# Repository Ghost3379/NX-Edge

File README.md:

# NX-Edge

> **Modular Embedded Development Platform**  
> *M.2 2260 Key B • 6-Layer Stackup • ESP32-S3 Dual-Core 240MHz • Autonomous LiPo Power-Path & Fuel Gauge • Dual-Antenna RF Front-End • 9-DOF IMU • I2S Audio Amp • 4-bit MicroSD*

---

<p align="center">
  <em>NX-Edge Top View — 100% single-sided top assembly with 45° ESP32-S3, QSPI Flash, BNO085 IMU, RV-3028 RTC, MAX98357A Audio Amp, MicroSD slot, LiPo Charger & Fuel Gauge.</em>
</p>

<p align="center">
  <em>NX-Edge Bottom View — Flat single-sided surface with M.2 Key B docking fingers, NO NVME warning, IMU coordinate triad, cut-safe jumpers [SW] & [LED], and GAIN test pad.</em>
</p>

---

> [!TIP]
> 📖 **Technical Documentation Available:**  
> * **[NX-Edge Hardware Reference Manual](docs/HARDWARE_MANUAL.md):** Detailed pinouts, subsystem floorplan, I2C register maps, power-path precautions, and quickstart code.
> * **[NX-Edge RF Design Guide](docs/RF_DESIGN_GUIDE.md):** 2.4 GHz transmission line impedance derivations ($Z_0 = 51.44\,\Omega$), stackup equations, and matching network BOM values.

---

## Overview

The **NX-Edge** is an embedded development board based on the ESP32-S3, built in an M.2 2260 form factor. It integrates power management, audio amplification, 9-DOF motion tracking, RTC, and microSD storage onto a single board, designed to interface with custom carrier boards via an M.2 Key B connector or edge breakout headers.

Built on a **6-layer PCB** with **100% single-sided component placement** (zero components on the bottom layer):

* **M.2 2260 Form Factor ($22 \times 60\text{ mm}$):** Fits the ESP32-S3 and all peripherals within the 60 mm board length.
* **M.2 Key B Edge Connector (75 pins):** Custom pinout routing power, audio, I2C, UART, SDMMC, and all free GPIOs to carrier boards.
* **Edge Breakouts (2.54 mm pitch):** 15 edge breakout holes for bench testing and wiring. The left side breaks out logic/power/I2C/UART, and the right side breaks out NeoPixel and speaker outputs.
* **Flat Bottom Surface:** 100% single-sided top assembly with zero components on the bottom, leaving the back flat for low-profile mounting.

> [!IMPORTANT]
> **NX Custom Maker Interconnect (Non-PC Hardware):**  
> While the board utilizes the standard mechanical **M.2 Key B form factor and connector**, the pinout is a **custom, high-power maker standard** (similar to SparkFun MicroMod). The M.2 connector routes raw battery power, high-current 5V rails, speaker outputs, and 3.3V GPIOs directly to custom carrier boards. **Do NOT plug this board into a standard PC motherboard M.2 NVMe/SATA slot.**

---

## Current Hardware Implementation Status

| Subsystem / Block | Status | Key Components & Implementation Details |
| :--- | :---: | :--- |
| **Compute Core** | **Routed** | ESP32-S3 (bare QFN-56 @ 45°), 40 MHz 2016 crystal with symmetrical wings, decoupling network on power rails. |
| **Flash Memory** | **Routed** | 16 MB Winbond `W25Q128JVPIQ` (WSON-8), inline decoupling, Quad-SPI bus routed on internal Layer 3 stripline. |
| **RF Front-End** | **Routed** | Ignion `NN02-201` ceramic antenna + Hirose U.FL receptacle + Infineon `BGS12WN6` SPDT RF switch (`RF_CTRL`). |
| **USB Type-C** | **Routed** | Reversible Type-C receptacle, `USBLC6-2SC6` ESD array, dual $5.1\,\text{k}\Omega$ CC pulldowns (`R20`/`R21`), D+/D- internal stripline. |
| **LiPo Charging** | **Routed** | TI `BQ25170` autonomous linear charger (600–800 mA), status LED, horizontal JST-PH 2.0mm connector (`P1`/`P2`). |
| **Battery Power Switch** | **Routed** | Solder jumper & switch pads `JP2` (`[ SW ]`) to wire a physical power toggle switch (must be ON to charge). |
| **Buck Regulator** | **Routed** | TI `TLV62569` synchronous buck converter delivering continuous **3.3V @ 2.0A** with low ripple. |
| **Fuel Gauge** | **Routed** | Maxim `MAX17048` ModelGauge™ I2C fuel gauge (`0x36`) for cell voltage ($V_{CELL}$) and SoC% without IR drop. |
| **NeoPixel Driver** | **Routed** | P-FET `Q2` (DMP3130L-7) + NPN `Q3` (BC847W) on `IO12` with 3 castellated pads (`VN`, `NPD_IN`, `GND`) for high-power strips. |
| **Onboard Indicators**| **Routed** | Onboard RGB NeoPixel (WS2812B/SK6812) powered from `VN` + User LED (LED13 / `D3`) with resistor `R13`. |
| **6-Layer Stackup** | **Routed** | 6-layer stackup with 0.45 mm / 0.25 mm standard through-hole vias for clean signal integrity. |
| **MicroSD Slot** | **Routed** | Molex 105162 push-pull slot running in native **4-bit hardware SDMMC** mode via dedicated internal stripline bus. |
| **Motion Sensor** | **Routed** | CEVA / Hillcrest Labs `BNO085` 9-DOF IMU with dedicated 32.768 kHz quartz crystal and sensor-fusion engine. |
| **Audio Amplifier** | **Routed** | Maxim `MAX98357A` I2S Class-D mono amplifier delivering up to 3.2W into 4Ω directly from `VIN` (Bridge-Tied Load speaker output). |
| **RTC Subsystem** | **Routed** | Micro Crystal `RV-3028-C7` extreme low-power ($45\,\text{nA}$) real-time clock with backup capacitor. |
| **Hardware Buttons** | **Routed** | Dual Alps `SKTAAAE010` ($0.53\text{ mm}$ height) tactile buttons for **BOOT** (`IO0`) and **RST** with hardware Power-On-Reset (POR) delay circuit. |
| **Routing Status** | **100% Complete** | 100% routed on all 6 layers using **standard through-hole vias only** (0 blind, 0 buried). |

---

## 6-Layer Stackup Architecture

To ensure signal integrity and separate the 2.4 GHz RF stage from digital signal buses, the NX-Edge uses a **6-layer symmetrical stackup**:

| Layer | KiCad Layer | Type | Copper Role & Signal Integrity Function |
| :---: | :---: | :---: | :--- |
| **L1** | `F.Cu` | Mixed / Top | Component mounting, 2.4 GHz RF transmission line, localized power pours (`VIN`, `+3V3`, `VBAT`). |
| **L2** | `In1.Cu` | Plane | **Solid Ground Plane (GND):** Return path and shield directly below Top layer. |
| **L3** | `In2.Cu` | Stripline Sig | **Internal Signals:** Shielded striplines for **USB D+/D-**, **Flash Quad-SPI**, and **SDMMC**. |
| **L4** | `In3.Cu` | Power Plane | **Power Plane Mosaic:** Low-impedance internal distribution for `+3V3`, `VBUS`, and `VBAT`. |
| **L5** | `In4.Cu` | Plane | **Secondary Solid Ground Plane (GND):** Complete ground shield referencing Bottom layer. |
| **L6** | `B.Cu` | Mixed / Bottom | Non-critical escape routing, switched `VN` power plane, M.2 docking fingers, and edge test pads. |

* **Via Geometry & Cost Efficiency:** Optimized to **0.45 mm pad diameter / 0.25 mm drill hole** (0.1 mm annular ring). The entire board is routed using **standard through-hole vias only** (0 blind, 0 buried, and 0 laser micro-vias), keeping prototype fabrication compatible with standard, low-cost fab pools.

---

## Power Architecture & Power-Path Topology

The NX-Edge implements an autonomous, low-loss **Power-Path management architecture**:

```text
  USB-C (VBUS 5V) ──► [Schottky D2] ──────────┐
                                              │
  LiPo (VBAT) ────► [Hard-Cut JP2] ──► [Q1] ──┴─► [ VIN ] (Automatic System Rail)
                                        ▲           │
                                        │ Gate      ├─► [TLV62569 Buck] ──► +3V3 (2.0A)
                                  (VBUS Controlled) │
                                                    ├─► [MAX17048 Gauge] (I2C SoC Monitoring)
                                                    │
                                                    └─► [Q2 P-FET / Q3 NPN] ──► VN (Switched NeoPixel Rail)
                                                              ▲
                                                              │ GPIO12 (CTRL_NP)
```

1. **Automatic Power-Path Node (`VIN`):**
   * Sourced through Schottky diode from USB `VBUS` ($5.0\text{V}$) or low-loss P-MOSFET from battery `VBAT` ($3.7\text{–}4.2\text{V}$).
   * **USB Connected:** `VBUS` holds the P-FET gate high, completely isolating the battery from system discharge. `VIN` runs directly on USB power ($\approx 4.8\text{–}5.0\text{V}$).
   * **Battery Only:** When USB is disconnected, a gate pull-down immediately engages the P-FET ($R_{DS(on)} \approx 30\text{ m}\Omega$), supplying `VIN` with virtually zero voltage drop.
2. **System Buck Regulator (`TLV62569`):**
   * Synchronous step-down buck converter delivering **$3.3\text{V} @ \mathbf{2.0\text{A}}$ continuous** with $>95\%$ efficiency.
   * Powers the ESP32-S3, Flash, sensors, and peripherals cleanly without thermal throttling.
3. **Autonomous LiPo Charger (`BQ25170`):**
   * Standalone linear charger powered from `VBUS` configured for $600\text{–}800\text{ mA}$ charging with NTC thermistor input.
   * **Decoupled Charging:** Because the system and external LEDs run from `VIN`, charging current is never hijacked by system load.
4. **ModelGauge™ Fuel Gauge (`MAX17048`):**
   * Precision I2C fuel gauge (`0x36`) monitoring cell voltage directly at the battery connector. Reports cell voltage ($V_{CELL}$ in mV), State of Charge (SOC %), and rate of change over I2C without needing external ADC dividers.
5. **Smart NeoPixel Power-Cut (`VN`):**
   * High-side P-MOSFET `Q2` driven by NPN BJT `Q3` controlled via **GPIO12 (`CTRL_NP`)**.
   * In Standby/Deep Sleep (`CTRL_NP = LOW`), power to both onboard and external NeoPixels is cut to $0.0\text{V}$, eliminating quiescent current draw.

---

## RF Front-End & Antenna Switch

* **RF Switch:** Infineon **`BGS12WN6`** SPDT switch ($0.7 \times 1.1\text{ mm}$) rated up to $6\text{ GHz}$ with $<0.3\text{ dB}$ insertion loss.
* **50Ω Transmission Lines:** All RF lines routed on `F.Cu` with $W = 0.150\,\text{mm}$ over $0.100\,\text{mm}$ prepreg ($Z_0 = 51.44\,\Omega$, $\text{VSWR} = 1.028:1$). See the **[RF Design Guide](docs/RF_DESIGN_GUIDE.md)** for detailed math and matching BOM values.
* **Control:** Controlled via **`RF_CTRL`** (`GPIO10`):
  * **Low (Default):** On-board high-efficiency **Ignion NN02-201** ceramic chip antenna with 50Ω lumped matching network (`C13`, `L3`, `L2`).
  * **High:** Micro-coaxial **Hirose U.FL / IPEX** receptacle for external antenna routing out of metal, carbon fiber, or shielded enclosures.

---

## Mechanical Specifications

* **Form Factor:** M.2 2260 Key B ($22.0\text{ mm} \times 60.0\text{ mm}$).
* **Connector Type:** 75-pin M.2 Key B card edge connector.
* **PCB Thickness:** **$0.80\,\text{mm} \pm 10\%$** ($0.8\text{ mm}$ finished thickness, compliant with the official PCI-SIG M.2 Card Electromechanical Specification).
* **Component Clearance:** 100% single-sided top placement. Completely flat bottom surface (Zero-Z) for ultra-low-profile carrier mounting.
* **Silkscreen & Hardware Annotations:**
  * **`NO NVME`** boxed warning over bottom gold fingers to prevent accidental insertion into standard PC motherboard slots.
  * Dual-purpose **`B ▽`** marker designating both `SW2` (BOOT) and the mechanical Key B notch.
  * **`[ SW ]`** (`JP2`) and **`[ LED ]`** (`JP1`) boxed cut-jumpers with internal copper keepouts beneath the cut bridge.
  * **`G`** silkscreen marking audio GAIN test point `TP1`.
  * IMU 3-axis coordinate triad ($X, Y, Z$) and chip boundary outline.
  * MicroSD card insertion icon with contact orientation.
* **Edge Breakouts (2.54 mm pitch):** 15 edge breakout holes:
  * **Left Edge (Logic/Power):** `J9` (6-pin: `3V3`, `GND`, `RST`, `IO0`, `IO1`, `IO11`) and `J5` (4-pin: `IO8`/SDA, `IO9`/SCL, `RX`, `TX`).
  * **Right Edge (Power/Audio):** `J7` (3-pin: NeoPixel `VN`, `NPD_IN`, `GND`) and `J2` (2-pin: Speaker `Audio+`, `Audio-`).
  * *Breadboard & Prototyping Note:* While each individual rail uses standard 2.54 mm pitch and both sides align at the exact same height, the $22.0\text{ mm}$ board width is dictated by the M.2 standard and does not fall on a 2.54 mm grid ($22\text{ mm} \approx 8.66\text{ pitches}$). Vertical pin headers populated on both edges simultaneously will not span a single breadboard across the center ravine.  
    **Recommendation:** Solder pin headers to the IO/logic side (`J9`/`J5`) to plug into a breadboard. For the power/output side (`J7` NeoPixel and `J2` Audio), direct wire soldering or fly-leads are recommended anyway for power delivery and signal integrity—or simply leave them unpopulated if not needed.

---

## License & Credits

* **Hardware Design:** Licensed under the [CERN Open Hardware Licence Version 2 - Strongly Reciprocal (CERN-OHL-S)](https://ohwr.org/cernohl).
* **Engineering & Ownership:** Conceptualized, engineered, schematics, PCB layout, and testing by [@Ghost3379](https://github.com/Ghost3379).
* **Tooling & AI Transparency:** Antigravity IDE (Gemini 3.8) was used for brainstorming and documentation assistance. All hardware architecture, schematics, routing, and layout decisions are 100% human-designed and verified.

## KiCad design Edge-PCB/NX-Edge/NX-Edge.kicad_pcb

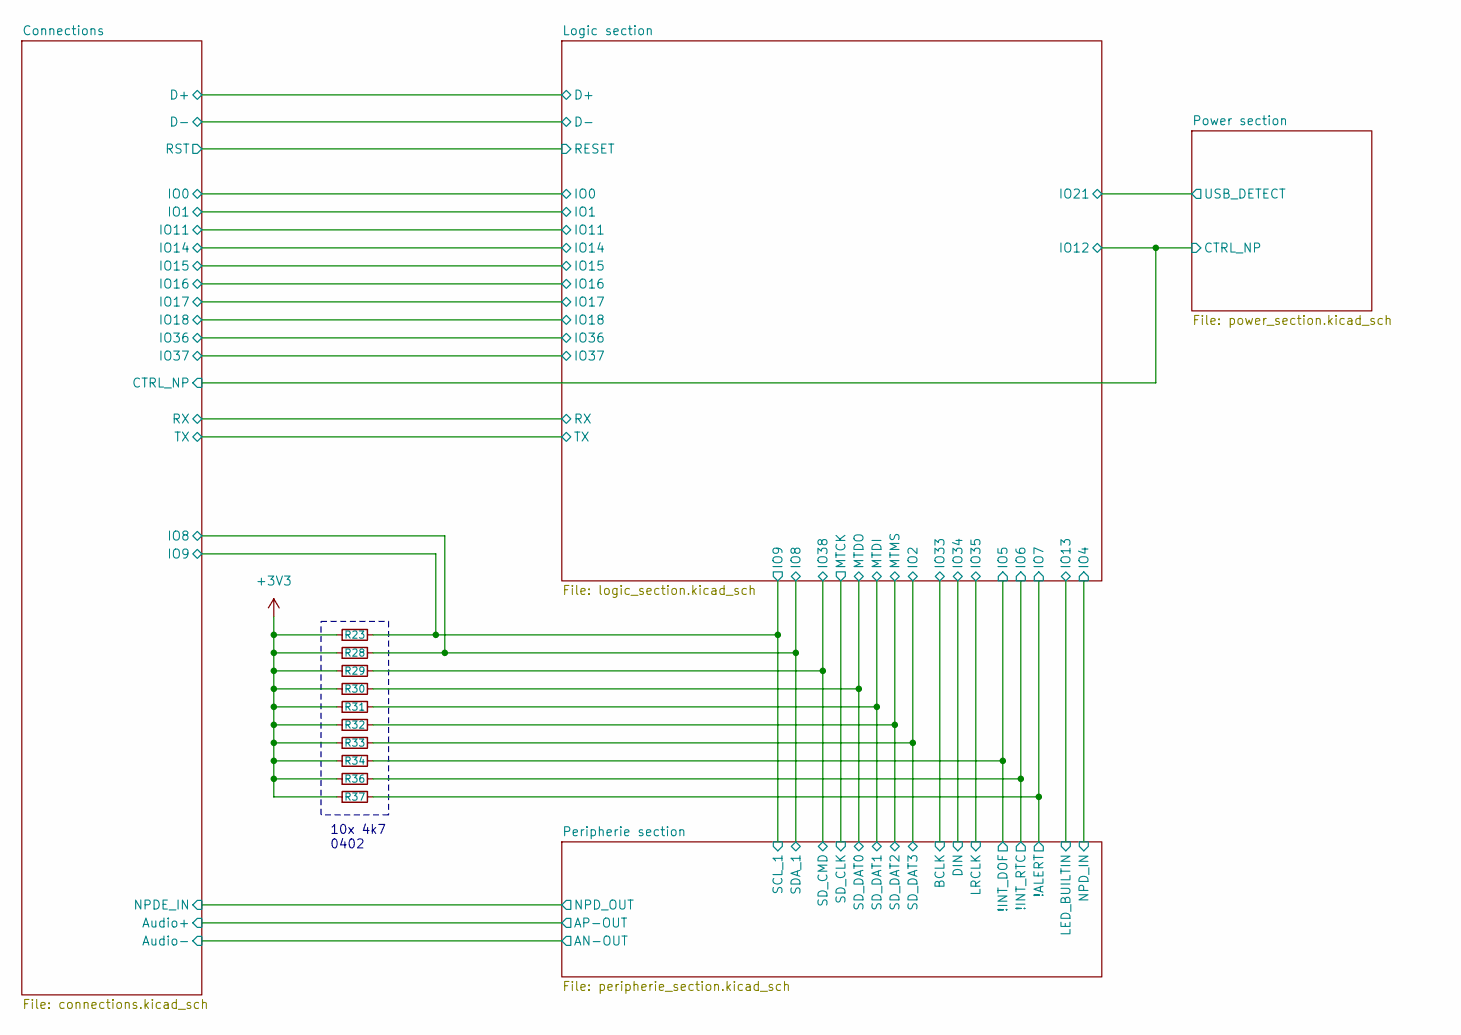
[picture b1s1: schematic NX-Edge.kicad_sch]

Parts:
R23, R28, R29, R30, R31, R32, R33, R34, R36, R37: 4k7; R_0402_1005Metric

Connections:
+3V3: R23.1, R28.1, R29.1, R30.1, R31.1, R32.1, R33.1, R34.1, R36.1, R37.1; also elsewhere on the board
/Connections/IO8: R28.2; also elsewhere on the board
/Connections/IO9: R23.2; also elsewhere on the board
/Logic section/IO2: R33.2; also elsewhere on the board
/Logic section/IO5: R34.2; also elsewhere on the board
/Logic section/IO6: R36.2; also elsewhere on the board
/Logic section/IO7: R37.2; also elsewhere on the board
/Logic section/IO38: R29.2; also elsewhere on the board
/Logic section/MTDI: R31.2; also elsewhere on the board
/Logic section/MTDO: R30.2; also elsewhere on the board
/Logic section/MTMS: R32.2; also elsewhere on the board

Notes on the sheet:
10x 4k7 0402

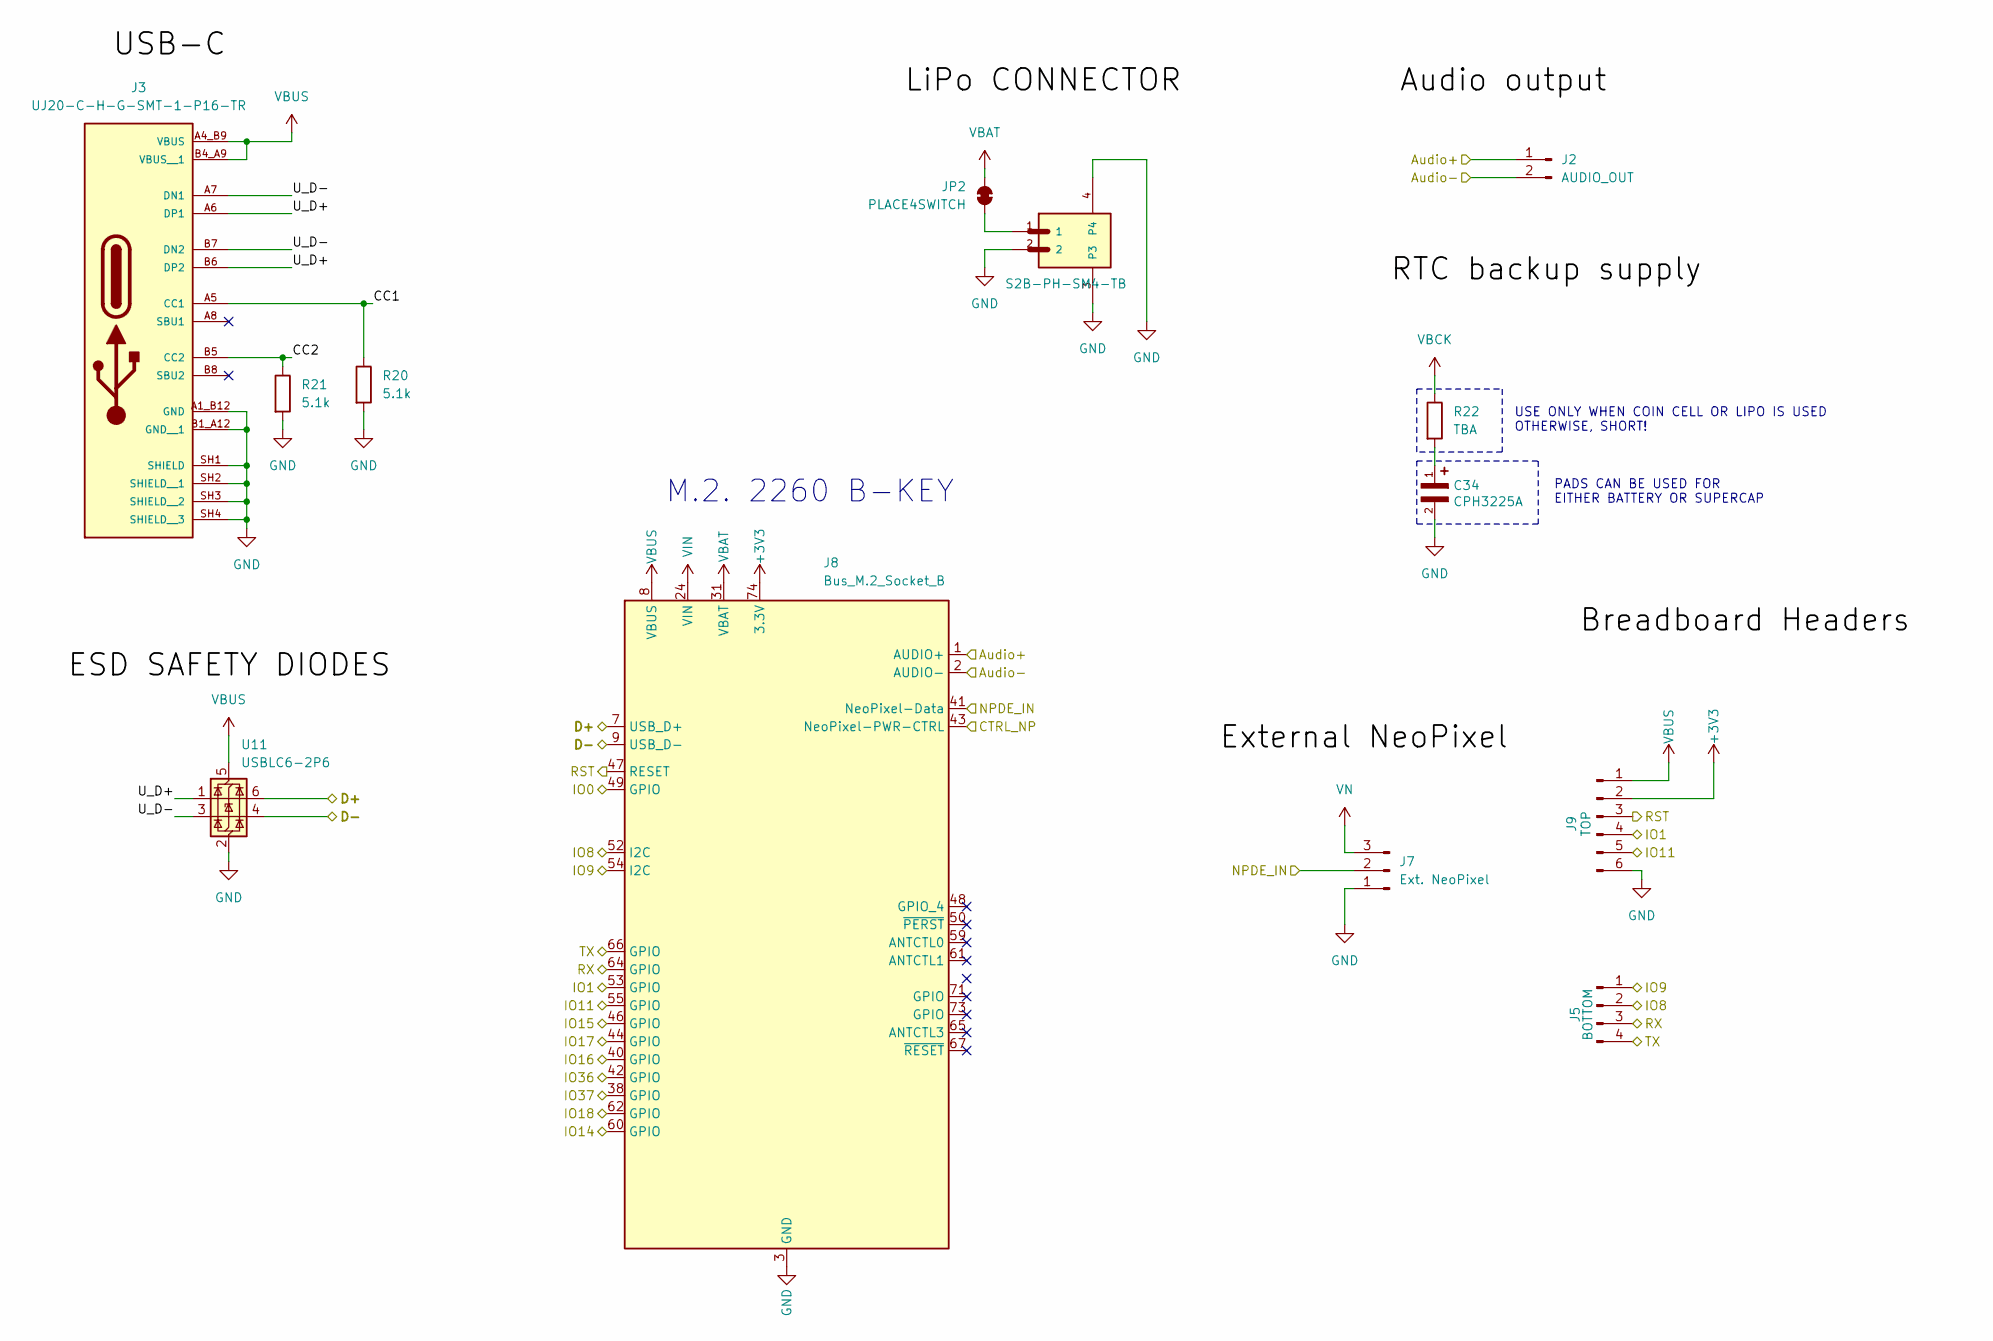
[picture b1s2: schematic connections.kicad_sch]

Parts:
C34: CPH3225A; CAPCP3225X100N
J2: AUDIO_OUT; PinHeader_1x02_P2.54mm_Vertical
J3: UJ20-C-H-G-SMT-1-P16-TR; SAMESKY_UJ20-C-H-G-SMT-1-P16-TR; PARTREV 1.0
J5: BOTTOM; PinHeader_1x04_P2.54mm_Vertical
J7: Ext. NeoPixel; PinHeader_1x03_P2.54mm_Vertical
J8: Bus_M.2_Socket_B; M.2_2260-xx-B
J9: TOP; PinHeader_1x06_P2.54mm_Vertical
JP2: PLACE4SWITCH; SolderJumper-2_P1.3mm_Bridged_Pad1.0x1.5mm
P1: S2B-PH-SM4-TB; JST_S2B-PH-SM4-TB
R20, R21: 5.1k; R_0402_1005Metric
R22: TBA; R_0402_1005Metric
U11: USBLC6-2P6; SOT-666

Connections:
+3V3: J8.68 (3.3V), J8.70 (3.3V), J8.72 (3.3V), J8.74 (3.3V), J9.2; also elsewhere on the board
/Connections/Audio+: J2.1, J8.1 (AUDIO+); also elsewhere on the board
/Connections/Audio-: J2.2, J8.2 (AUDIO-); also elsewhere on the board
/Connections/CC1: J3.A5 (CC1), R20.1
/Connections/CC2: J3.B5 (CC2), R21.1
/Connections/CTRL_NP: J8.43 (NeoPixel-PWR-CTRL); also elsewhere on the board
/Connections/D+: J8.7 (USB_D+), U11.6 (I/O1); also elsewhere on the board
/Connections/D-: J8.9 (USB_D-), U11.4 (I/O2); also elsewhere on the board
/Connections/IO0: J8.49 (GPIO); also elsewhere on the board
/Connections/IO1: J8.53 (GPIO), J9.4; also elsewhere on the board
/Connections/IO8: J5.2, J8.52 (I2C); also elsewhere on the board
/Connections/IO9: J5.1, J8.54 (I2C); also elsewhere on the board
/Connections/IO11: J8.55 (GPIO), J9.5; also elsewhere on the board
/Connections/IO14: J8.60 (GPIO); also elsewhere on the board
/Connections/IO15: J8.46 (GPIO); also elsewhere on the board
/Connections/IO16: J8.40 (GPIO); also elsewhere on the board
/Connections/IO17: J8.44 (GPIO); also elsewhere on the board
/Connections/IO18: J8.62 (GPIO); also elsewhere on the board
/Connections/IO36: J8.42 (GPIO); also elsewhere on the board
/Connections/IO37: J8.38 (GPIO); also elsewhere on the board
/Connections/NPDE_IN: J7.2, J8.41 (NeoPixel-Data); also elsewhere on the board
/Connections/RST: J8.47 (RESET), J9.3; also elsewhere on the board
/Connections/RX: J5.3, J8.64 (GPIO); also elsewhere on the board
/Connections/TX: J5.4, J8.66 (GPIO); also elsewhere on the board
/Connections/U_D+: J3.A6 (DP1), J3.B6 (DP2), U11.1 (I/O1)
/Connections/U_D-: J3.A7 (DN1), J3.B7 (DN2), U11.3 (I/O2)
GND: C34.2, J3.A1_B12 (GND), J3.B1_A12 (GND__1), J3.SH1 (SHIELD), J3.SH2 (SHIELD__1), J3.SH3 (SHIELD__2), J3.SH4 (SHIELD__3), J7.1, J8.3 (GND), J8.5 (GND), J8.11 (GND), J8.21 (GND), J8.23 (GND), J8.25 (GND), J8.27 (GND), J8.28 (GND), J8.29 (GND), J8.30 (GND), J8.32 (GND), J8.34 (GND), J8.36 (GND), J8.39 (GND), J8.45 (GND), J8.51 (GND), J8.57 (GND), J8.63 (GND), J8.69 (GND), J8.75 (GND), J9.6, P1.2, P1.3, P1.4, R20.2, R21.2, U11.2 (GND); also elsewhere on the board
unnamed: C34.1, R22.2
unnamed: JP2.2 (B), P1.1
VBAT: J8.31 (VBAT), J8.33 (VBAT), J8.35 (VBAT), J8.37 (VBAT), JP2.1 (A); also elsewhere on the board
VBCK: R22.1; also elsewhere on the board
VBUS: J3.A4_B9 (VBUS), J3.B4_A9 (VBUS__1), J8.4 (VBUS), J8.6 (VBUS), J8.8 (VBUS), J8.10 (VBUS), J9.1, U11.5 (VBUS); also elsewhere on the board
VIN: J8.20 (VIN), J8.22 (VIN), J8.24 (VIN), J8.26 (VIN); also elsewhere on the board
VN: J7.3; also elsewhere on the board

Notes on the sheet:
USE ONLY WHEN COIN CELL OR LIPO IS USED OTHERWISE, SHORT!
PADS CAN BE USED FOR EITHER BATTERY OR SUPERCAP
M.2. 2260 B-KEY

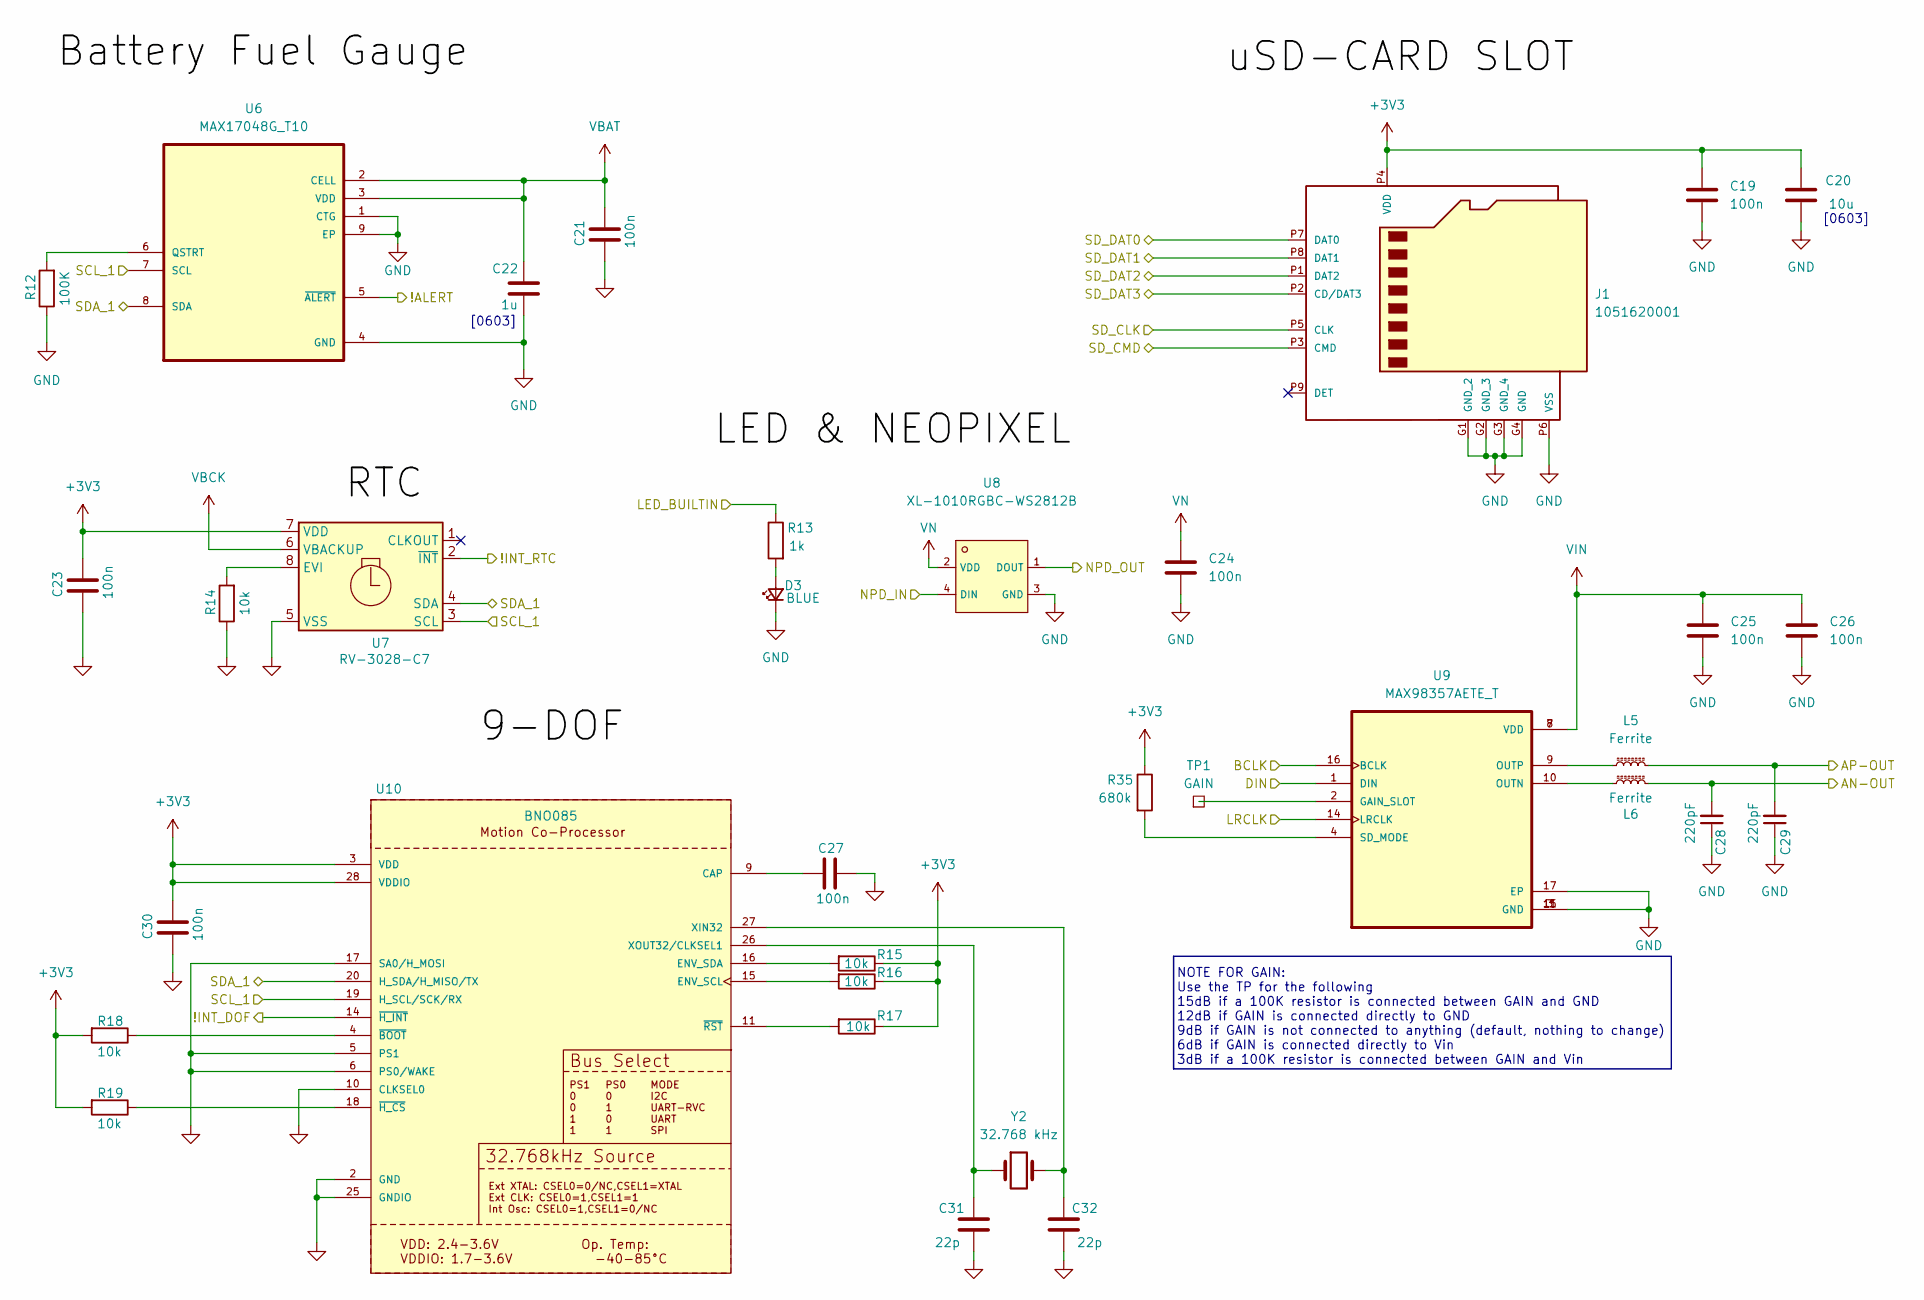
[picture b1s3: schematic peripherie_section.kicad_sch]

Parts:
C19, C21, C23, C24, C25, C26, C27, C30: 100n; C_0402_1005Metric
C20: 10u; C_0603_1608Metric
C22: 1u; C_0603_1608Metric
C28, C29: 220pF; C_0603_1608Metric_Pad1.08x0.95mm_HandSolder
C31, C32: 22p; C_0402_1005Metric
D3: BLUE; LED_0603_1608Metric
J1: 1051620001; 105162-0001_MOL; MANUFACTURER_PART_NUMBER 1051620001
L5, L6: Ferrite; L_0603_1608Metric_Pad1.05x0.95mm_HandSolder
R12: 100K; R_0402_1005Metric
R13: 1k; R_0402_1005Metric
R14, R15, R16, R17, R18, R19: 10k; R_0402_1005Metric
R35: 680k; R_0402_1005Metric
TP1: GAIN; SolderWirePad_1x01_SMD_1x2mm
U6: MAX17048G_T10; SON50P200X200X80-9N
U7: RV-3028-C7; MicroCrystal_C7_SON-8_1.5x3.2mm_P0.9mm
U8: XL-1010RGBC-WS2812B; LED-SMD_4P-L1.0-W1.0-TL_XL-1010RGBC-WS2812B; LCSC C5349953
U9: MAX98357AETE_T; QFN50P300X300X80-17N
U10: BNO085; IC_BNO085; PARTREV v1.17
Y2: 32.768 kHz; Crystal_SMD_3215-2Pin_3.2x1.5mm; Tolerance ±20ppm; Manufacterer part number DH2032K768C5T1521011

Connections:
+3V3: C19.1, C20.1, C23.1, C30.1, J1.P4 (VDD), R15.1, R16.1, R17.1, R18.2, R19.2, R35.1, U7.7 (VDD), U10.3 (VDD), U10.28 (VDDIO); also elsewhere on the board
/Connections/Audio+: C29.2, L5.2; also elsewhere on the board
/Connections/Audio-: C28.2, L6.2; also elsewhere on the board
/Connections/IO8: U6.8 (SDA), U7.4 (SDA), U10.20 (H_SDA/H_MISO/TX); also elsewhere on the board
/Connections/IO9: U6.7 (SCL), U7.3 (SCL), U10.19 (H_SCL/SCK/RX); also elsewhere on the board
/Connections/NPDE_IN: U8.1 (DOUT); also elsewhere on the board
/Logic section/IO2: J1.P2 (CD/DAT3); also elsewhere on the board
/Logic section/IO4: U8.4 (DIN); also elsewhere on the board
/Logic section/IO5: U10.14 (~H_INT); also elsewhere on the board
/Logic section/IO6: U7.2 (~INT); also elsewhere on the board
/Logic section/IO7: U6.5 (~ALERT); also elsewhere on the board
/Logic section/IO13: R13.1; also elsewhere on the board
/Logic section/IO33: U9.16 (BCLK); also elsewhere on the board
/Logic section/IO34: U9.1 (DIN); also elsewhere on the board
/Logic section/IO35: U9.14 (LRCLK); also elsewhere on the board
/Logic section/IO38: J1.P3 (CMD); also elsewhere on the board
/Logic section/MTCK: J1.P5 (CLK); also elsewhere on the board
/Logic section/MTDI: J1.P8 (DAT1); also elsewhere on the board
/Logic section/MTDO: J1.P7 (DAT0); also elsewhere on the board
/Logic section/MTMS: J1.P1 (DAT2); also elsewhere on the board
GND: C19.2, C20.2, C21.2, C22.2, C23.2, C24.2, C25.2, C26.2, C27.1, C28.1, C29.1, C30.2, C31.2, C32.2, D3.1 (K), J1.G1 (GND_2), J1.G2 (GND_3), J1.G3 (GND_4), J1.G4 (GND), J1.P6 (VSS), R12.1, R14.1, U6.1 (CTG), U6.4 (GND), U6.9 (EP), U7.5 (VSS), U8.3 (GND), U9.3 (GND), U9.11 (GND), U9.15 (GND), U9.17 (EP), U10.2 (GND), U10.5 (PS1), U10.6 (PS0/WAKE), U10.10 (CLKSEL0), U10.17 (SA0/H_MOSI), U10.25 (GNDIO); also elsewhere on the board
unnamed: D3.2 (A), R13.2
unnamed: R12.2, U6.6 (QSTRT)
unnamed: R14.2, U7.8 (EVI)
unnamed: TP1.1 (1_1), U9.2 (GAIN_SLOT)
unnamed: L6.1, U9.10 (OUTN)
unnamed: L5.1, U9.9 (OUTP)
unnamed: R35.2, U9.4 (SD_MODE)
unnamed: C27.2, U10.9 (CAP)
unnamed: R16.2, U10.15 (ENV_SCL)
unnamed: R15.2, U10.16 (ENV_SDA)
unnamed: C32.1, U10.27 (XIN32), Y2.2
unnamed: C31.1, U10.26 (XOUT32/CLKSEL1), Y2.1
unnamed: R18.1, U10.4 (~BOOT)
unnamed: R19.1, U10.18 (~H_CS)
unnamed: R17.2, U10.11 (~RST)
VBAT: C21.1, C22.1, U6.2 (CELL), U6.3 (VDD); also elsewhere on the board
VBCK: U7.6 (VBACKUP); also elsewhere on the board
VIN: C25.1, C26.1, U9.7 (VDD), U9.8 (VDD); also elsewhere on the board
VN: C24.1, U8.2 (VDD); also elsewhere on the board

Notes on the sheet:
[0603]
NOTE FOR GAIN: Use the TP for the following 15dB if a 100K resistor is connected between GAIN and GND 12dB if GAIN is connected directly to GND 9dB if GAIN is not connected to anything (default, nothing to change) 6dB if GAIN is connected directly to Vin 3dB if a 100K resistor is connected between 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

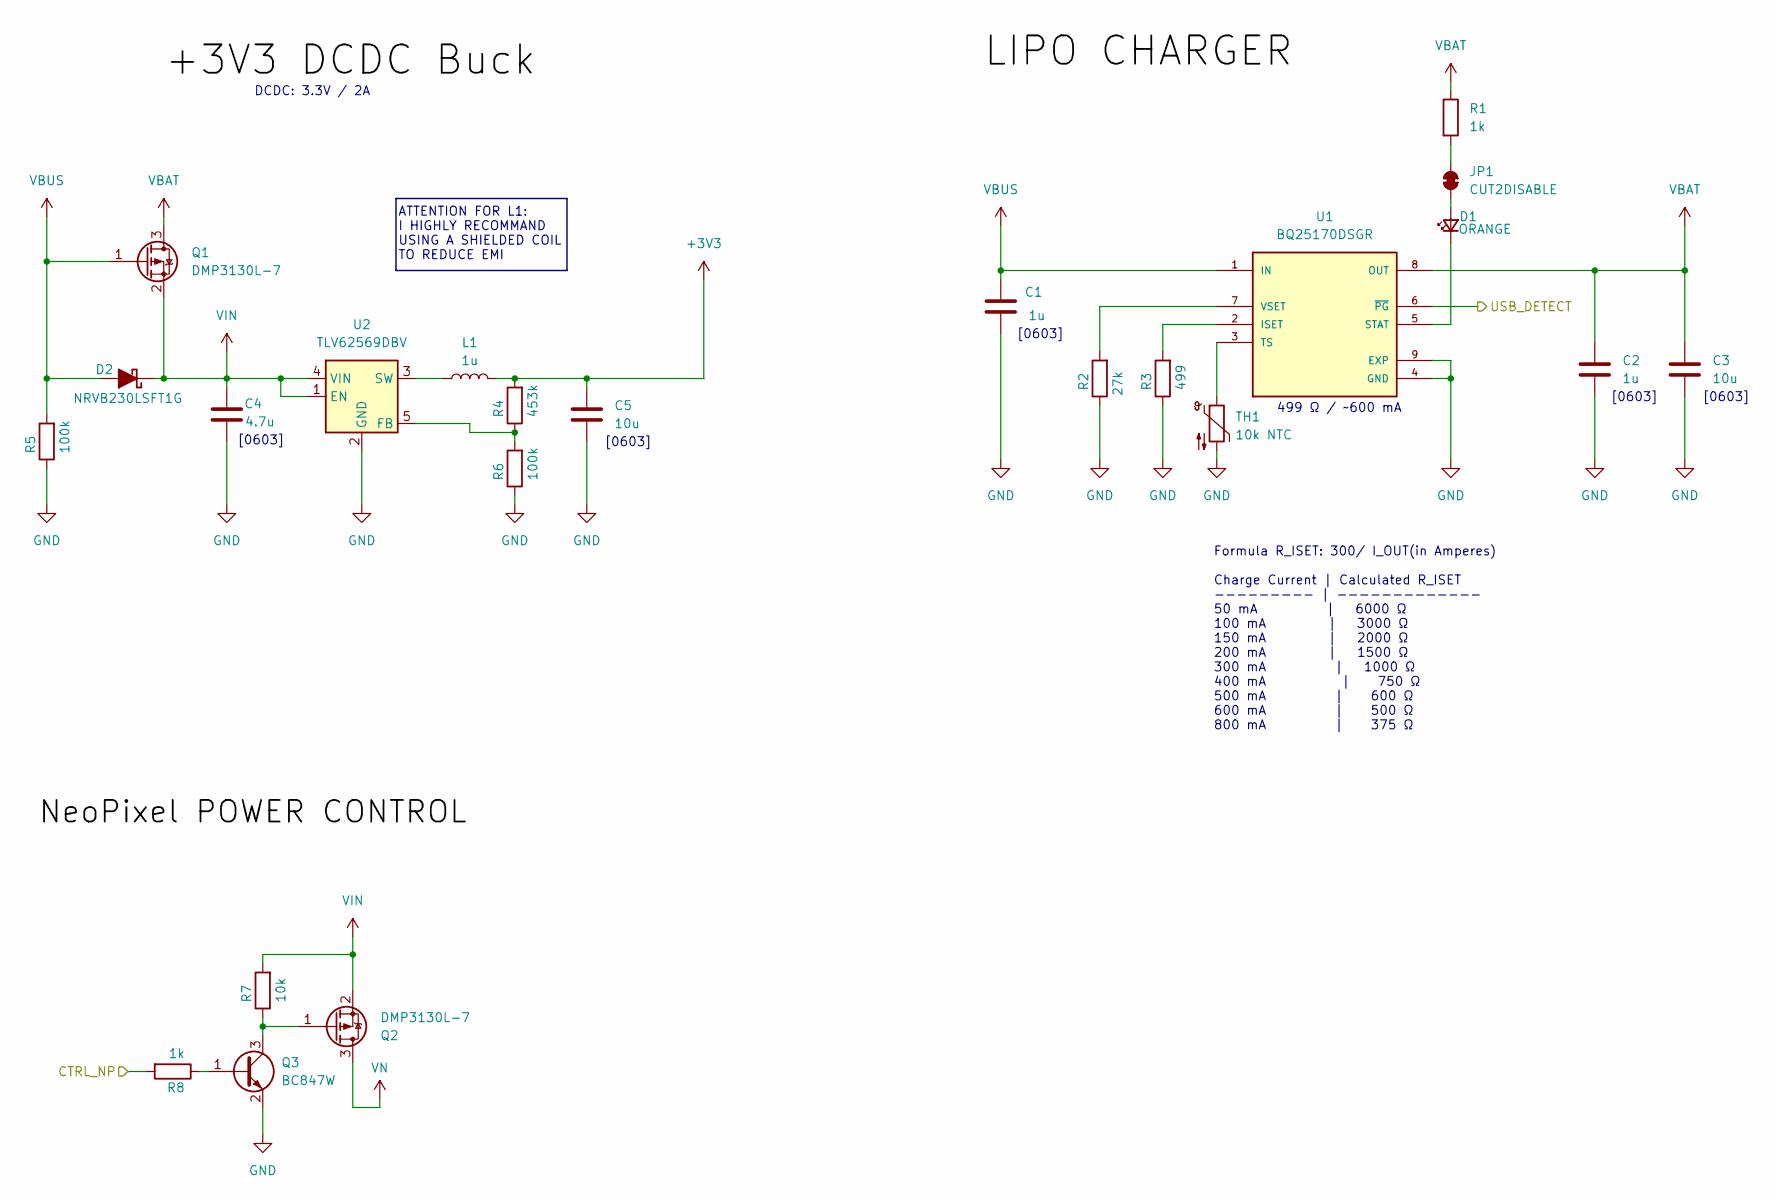
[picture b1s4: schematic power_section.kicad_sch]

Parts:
C1, C2: 1u; C_0603_1608Metric
C3, C5: 10u; C_0603_1608Metric
C4: 4.7u; C_0603_1608Metric
D1: ORANGE; LED_0603_1608Metric
D2: NRVB230LSFT1G; D_SOD-123
JP1: CUT2DISABLE; SolderJumper-2_P1.3mm_Bridged_Pad1.0x1.5mm
L1: 1u; L_1008_2520Metric; Manufacturer part number SRN2510BTA-1R0M
Q1, Q2: DMP3130L-7; SOT-23
Q3: BC847W; SOT-323_SC-70
R1, R8: 1k; R_0402_1005Metric
R2: 27k; R_0402_1005Metric
R3: 499; R_0402_1005Metric
R4: 453k; R_0402_1005Metric
R5, R6: 100k; R_0402_1005Metric
R7: 10k; R_0402_1005Metric
TH1: 10k NTC; R_0402_1005Metric; Manufacturer part number NCU15XH103D60RC
U1: BQ25170DSGR; SON50P200X200X80-9N; PARTREV A
U2: TLV62569DBV; SOT-23-5

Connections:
+3V3: C5.1, L1.2, R4.2; also elsewhere on the board
/Connections/CTRL_NP: R8.2; also elsewhere on the board
/Logic section/IO21: U1.6 (~PG); also elsewhere on the board
GND: C1.2, C2.2, C3.2, C4.2, C5.2, Q3.2 (E), R2.1, R3.1, R5.1, R6.1, TH1.2, U1.4 (GND), U1.9 (EXP), U2.2 (GND); also elsewhere on the board
unnamed: D1.2 (A), JP1.2 (B)
unnamed: D1.1 (K), U1.5 (STAT)
unnamed: JP1.1 (A), R1.2
unnamed: Q2.1 (G), Q3.3 (C), R7.1
unnamed: Q3.1 (B), R8.1
unnamed: R3.2, U1.2 (ISET)
unnamed: TH1.1, U1.3 (TS)
unnamed: R2.2, U1.7 (VSET)
unnamed: R4.1, R6.2, U2.5 (FB)
unnamed: L1.1, U2.3 (SW)
VBAT: C2.1, C3.1, Q1.3 (D), R1.1, U1.8 (OUT); also elsewhere on the board
VBUS: C1.1, D2.2 (A), Q1.1 (G), R5.2, U1.1 (IN); also elsewhere on the board
VIN: C4.1, D2.1 (K), Q1.2 (S), Q2.2 (S), R7.2, U2.1 (EN), U2.4 (VIN); also elsewhere on the board
VN: Q2.3 (D); also elsewhere on the board

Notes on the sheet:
499 Ω / ~600 mA
[0603]
Formula R_ISET: 300/ I_OUT(in Amperes) Charge Current | Calculated R_ISET --------- | ------------- 50 mA | 6000 Ω 100 mA | 3000 Ω 150 mA | 2000 Ω 200 mA | 1500 Ω 300 mA | 1000 Ω 400 mA | 750 Ω 500 mA | 600 Ω 600 mA | 500 Ω 800 mA | 375 Ω
ATTENTION FOR L1: I HIGHLY RECOMMAND USING A SHIELDED COIL TO REDUCE EMI
DCDC: 3.3V / 2A
